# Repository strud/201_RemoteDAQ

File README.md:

# 201_RemoteDAQ
DAQ module with wireless connectivity and local storage

Objectives
1. High resolution low noise analog input capture at rates of at least 5kHz
2. Suitable to take signal inputs of strain gauges/load cells and thermocouples directly without additional pre-amplification
3. At least 4 channels
4. Configuration, live view and download over wireless interface(s)
5. Low channel count (>= 4) of digital outputs, 5A capacity with self protection (ie against short cct)
6. Output channels to have continuity test inputs
7. Internall logging capability at full acquisition rate for at least 30s duration
8. logged file retrieval to be over wireless link &/or to removable SD card

Useful references

https://www.ti.com/product/ADS131M04

https://www.ti.com/lit/ug/sbau332a/sbau332a.pdf

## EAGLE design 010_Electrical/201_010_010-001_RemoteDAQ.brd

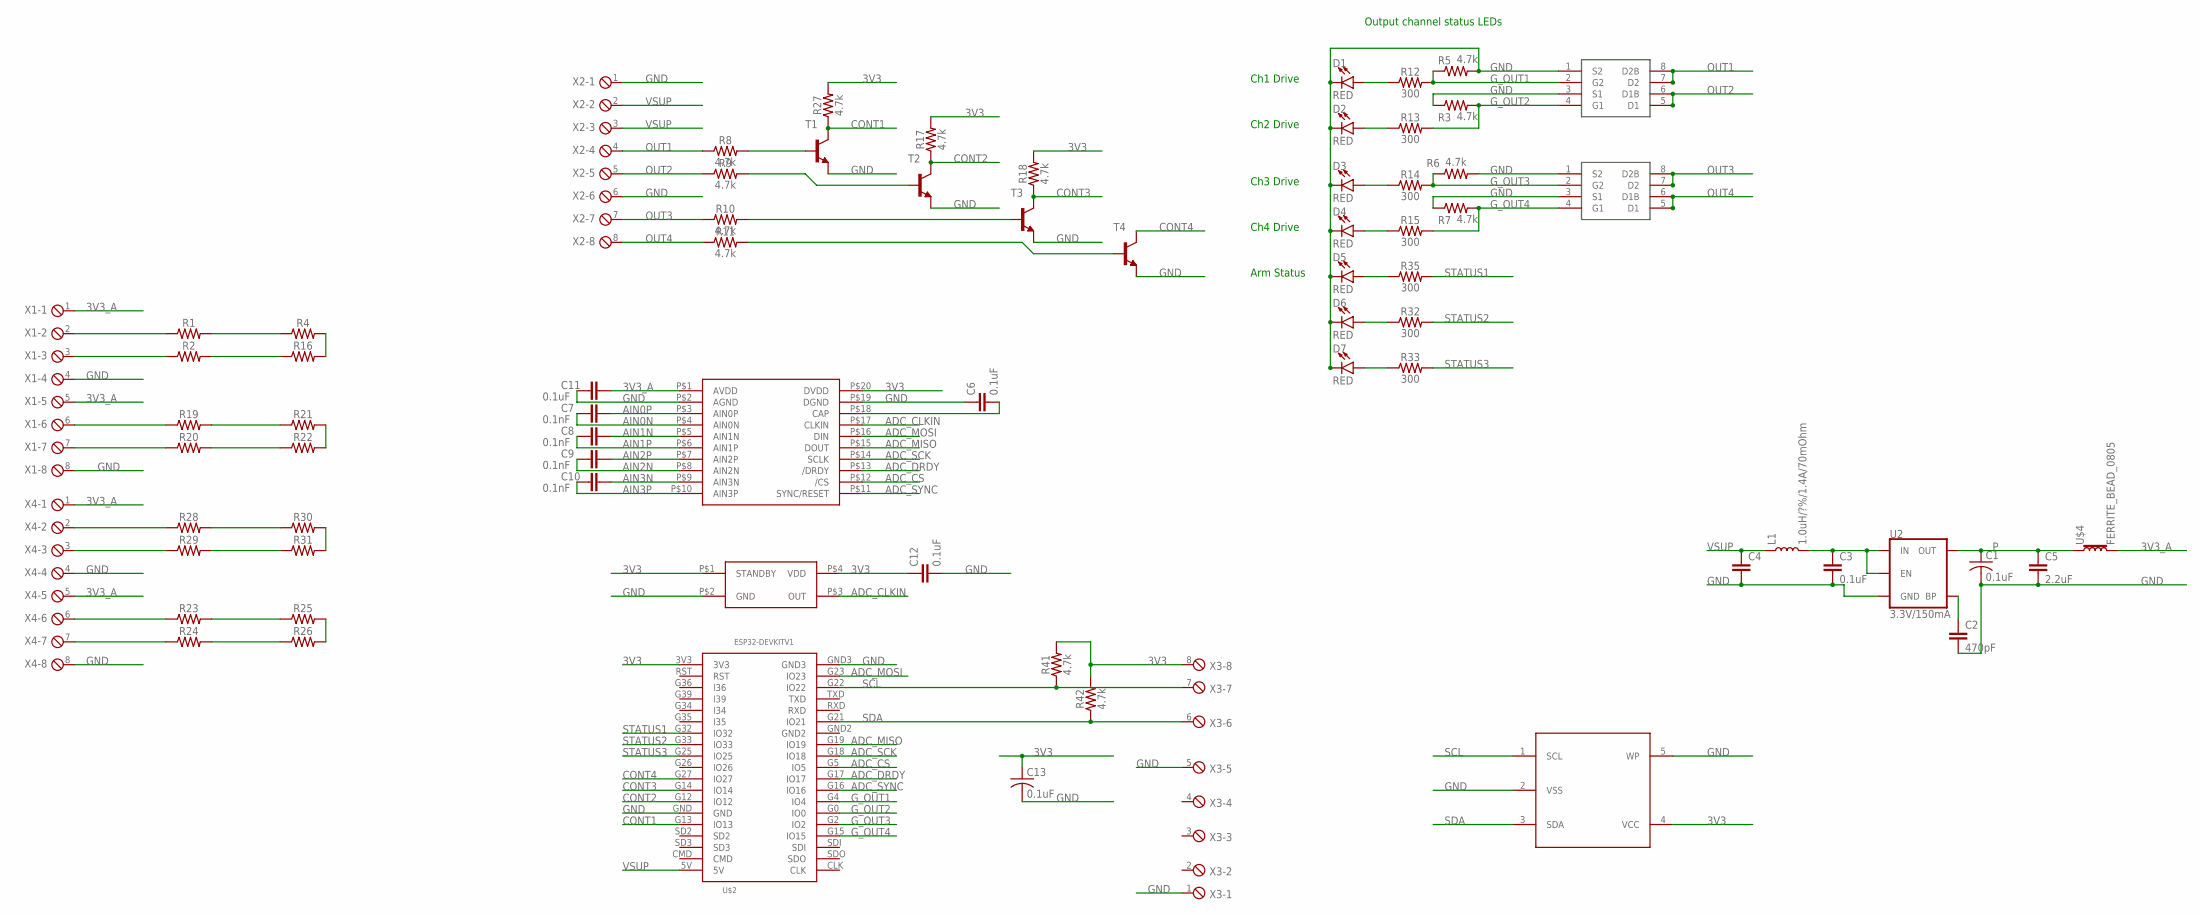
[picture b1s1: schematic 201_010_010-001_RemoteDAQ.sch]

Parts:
C1, C13: 0.1uF; C0603K
C2: 470pF; 0603
C3, C6, C11, C12: 0.1uF; 0603
C4: CAP-0603; 0603
C5: 2.2uF; 0805
C7, C8, C9, C10: 0.1nF; 0603
D1, D2, D3, D4, D5, D6, D7: RED; LED-0603
L1: 1.0uH/?%/1.4A/70mOhm; 0805-WIDE
R1, R2, R4, R16, R19, R20, R21, R22, R23, R24, R25, R26, R28, R29, R30, R31: 0603
R3, R5, R6, R7, R8, R9, R10, R11, R17, R18, R27, R41, R42: 4.7k; 0603
R12, R13, R14, R15, R32, R33, R35: 300; 0603
T1, T2, T3, T4: BC849-NPN-SOT23-BEC; SOT23-BEC
U2: 3.3V/150mA; SOT23-5
U$1: ADS131M04; TSSOP-20
U$2: ESP32DEVKITV1; ESP32-DEVKITV1
U$3, U$5: AO4806; SO08
U$4: FERRITE_BEAD_0805; 0805
U$6: DSC1033; 7X5_PP
U$7: 24AA16T; SOT23-5L
X1, X2, X3, X4: MPT8; 8POL254

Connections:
3V3: C12.1, C13.1, R17.2, R18.2, R27.2, R41.2, R42.2, U$1.P$20 (DVDD), U$2.3V3, U$6.P$1 (STANDBY), U$6.P$4 (VDD), U$7.4 (VCC), X3.8
3V3_A: C11.2, U$1.P$1 (AVDD), U$4.2, X1.1, X1.5, X4.1, X4.5
ADC_CLKIN: U$1.P$17 (CLKIN), U$6.P$3 (OUT)
ADC_CS: U$1.P$12 (/CS), U$2.G5 (IO5)
ADC_DRDY: U$1.P$13 (/DRDY), U$2.G17 (IO17)
ADC_MISO: U$1.P$15 (DOUT), U$2.G19 (IO19)
ADC_MOSI: U$1.P$16 (DIN), U$2.G23 (IO23)
ADC_SCK: U$1.P$14 (SCLK), U$2.G18 (IO18)
ADC_SYNC: U$1.P$11 (SYNC/RESET), U$2.G16 (IO16)
AIN0N: C7.1, R2.2, R16.1, U$1.P$4 (AIN0N)
AIN0P: C7.2, R1.2, R4.1, U$1.P$3 (AIN0P)
AIN1N: C8.2, R20.2, R22.1, U$1.P$5 (AIN1N)
AIN1P: C8.1, R19.2, R21.1, U$1.P$6 (AIN1P)
AIN2N: C9.1, R24.2, R26.1, U$1.P$8 (AIN2N)
AIN2P: C9.2, R23.2, R25.1, U$1.P$7 (AIN2P)
AIN3N: C10.2, R29.2, R31.1, U$1.P$9 (AIN3N)
AIN3P: C10.1, R28.2, R30.1, U$1.P$10 (AIN3P)
CONT1: R27.1, T1.C, U$2.G13 (IO13)
CONT2: R17.1, T2.C, U$2.G12 (IO12)
CONT3: R18.1, T3.C, U$2.G14 (IO14)
CONT4: T4.C, U$2.G27 (IO27)
GND: C1.2, C2.2, C3.2, C4.2, C5.2, C6.1, C11.1, C12.2, C13.2, D1.C, D2.C, D3.C, D4.C, D5.C, D6.C, D7.C, R3.1, R5.2, R6.2, R7.1, T1.E, T2.E, T3.E, T4.E, U2.2 (GND), U$1.P$2 (AGND), U$1.P$19 (DGND), U$2.GND, U$2.GND3, U$3.1 (S2), U$3.3 (S1), U$5.1 (S2), U$5.3 (S1), U$6.P$2 (GND), U$7.2 (VSS), U$7.5 (WP), X1.4, X1.8, X2.1, X2.6, X3.1, X3.5, X4.4, X4.8
G_OUT1: R5.1, R12.2, U$2.G4 (IO4), U$3.2 (G2)
G_OUT2: R3.2, R13.2, U$2.G0 (IO0), U$3.4 (G1)
G_OUT3: R6.1, R14.2, U$2.G2 (IO2), U$5.2 (G2)
G_OUT4: R7.2, R15.2, U$2.G15 (IO15), U$5.4 (G1)
unnamed: C2.1, U2.4 (BP)
unnamed: C3.1, L1.2, U2.1 (IN), U2.3 (EN)
unnamed: R8.2, T1.B
unnamed: R9.2, T2.B
unnamed: R1.1, X1.2
unnamed: R10.2, T3.B
unnamed: R11.2, T4.B
unnamed: D1.A, R12.1
unnamed: D2.A, R13.1
unnamed: R2.1, X1.3
unnamed: R19.1, X1.6
unnamed: D3.A, R14.1
unnamed: D4.A, R15.1
unnamed: C6.2, U$1.P$18 (CAP)
unnamed: R20.1, X1.7
unnamed: R4.2, R16.2
unnamed: R21.2, R22.2
unnamed: R28.1, X4.2
unnamed: R29.1, X4.3
unnamed: R25.2, R26.2
unnamed: R23.1, X4.6
unnamed: D5.A, R35.1
unnamed: R24.1, X4.7
unnamed: R30.2, R31.2
unnamed: D6.A, R32.1
unnamed: D7.A, R33.1
OUT1: R8.1, U$3.7 (D2), U$3.8 (D2B), X2.4
OUT2: R9.1, U$3.5 (D1), U$3.6 (D1B), X2.5
OUT3: R10.1, U$5.7 (D2), U$5.8 (D2B), X2.7
OUT4: R11.1, U$5.5 (D1), U$5.6 (D1B), X2.8
P: C1.1, C5.1, U2.5 (OUT), U$4.1
SCL: R41.1, U$2.G22 (IO22), U$7.1 (SCL), X3.7
SDA: R42.1, U$2.G21 (IO21), U$7.3 (SDA), X3.6
STATUS1: R35.2, U$2.G32 (IO32)
STATUS2: R32.2, U$2.G33 (IO33)
STATUS3: R33.2, U$2.G25 (IO25)
VSUP: C4.1, L1.1, U$2.5V, X2.2, X2.3

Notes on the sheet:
Output channel status LEDs
Ch1 Drive
Ch2 Drive
Ch3 Drive
Ch4 Drive
Arm Status

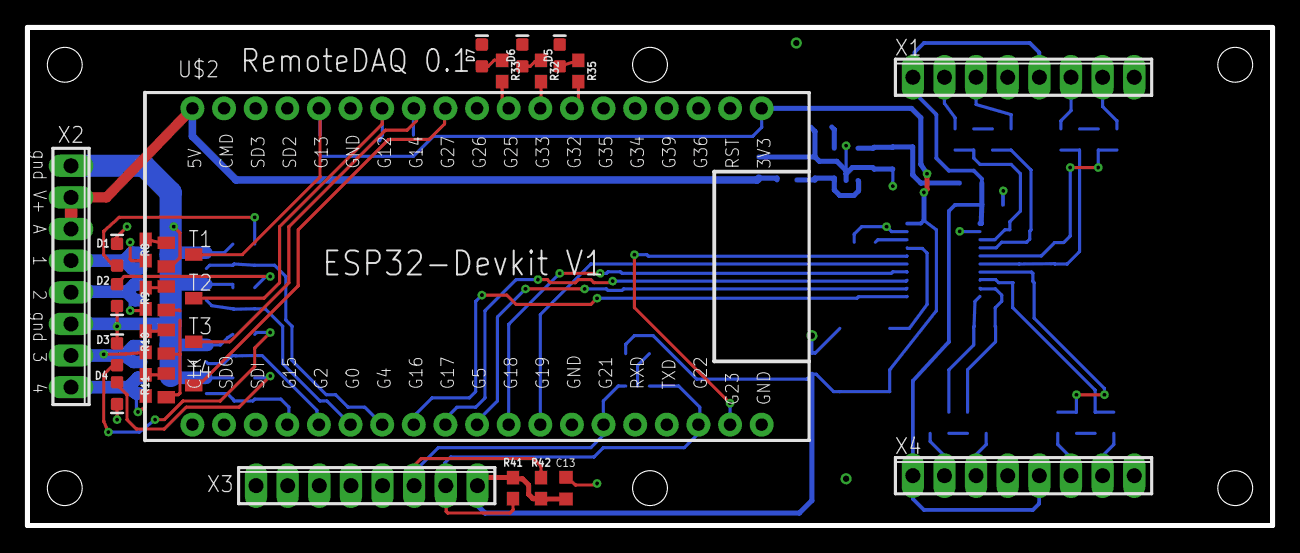
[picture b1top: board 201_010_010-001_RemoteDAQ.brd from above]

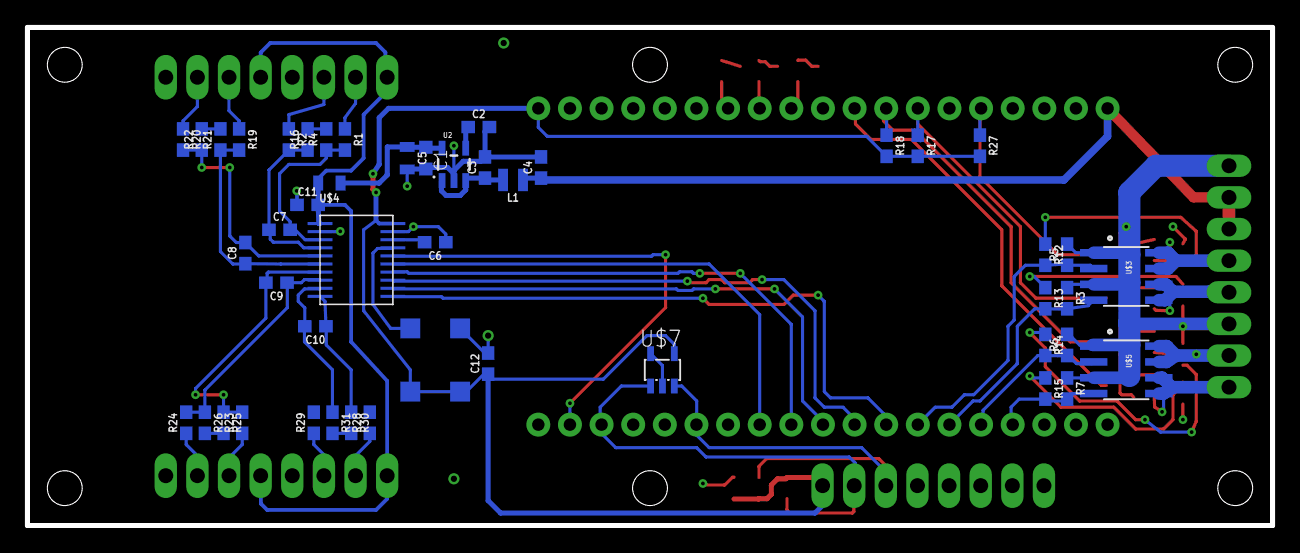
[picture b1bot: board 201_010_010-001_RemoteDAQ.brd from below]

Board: 2 copper layers, 100.0 x 40.0 mm, 73 parts (47 on the bottom side), 63 nets.

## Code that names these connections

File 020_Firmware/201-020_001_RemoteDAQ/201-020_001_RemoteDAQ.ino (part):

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    //#define SPARE   39
    //#define SPARE   34
    //#define SPARE_  35
    #define STATUS1   32
    #define STATUS2   33
    #define STATUS3   25   
    //#define SPARE    26
    #define Cont4Pin    27   // output ch4 continuity measurement
    #define Cont3Pin    14   // output ch3 continuity measurement
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    #define GOut3Pin    2  // output ch3 FET gate drive
    #define GOut2Pin    0  // output ch2 FET gate drive
    #define GOut1Pin    4   // output ch1 FET gate drive
    #define ADC_SYNC    16 // 
    #define ADC_DRDY    17 // 
    #define ADC_CS      5 // 
    #define ADC_SCK     18   // 
    #define ADC_MISO    19    //
    #define SDAPin      21
    #define SCLPin      22
    #define ADC_MOSI    23 // 

// forward declarations

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void updateContinuity(void){
if (digitalRead(Cont1Pin)==LOW) {
    sCont1 = "CC";
    Cont1 = 1;
  }
  else {
    sCont1 = "OC";
    Cont1=0;
  }
  if (digitalRead(Cont2Pin)==LOW) {
    sCont2 = "CC";
    Cont2 = 1;
  }
  else {
    sCont2 = "OC";
    Cont2=0;
  }if (digitalRead(Cont3Pin)==LOW) {
    sCont3 = "CC";
    Cont3 = 1;
  }
  else {
    sCont3 = "OC";
    Cont3=0;
  }
  if (digitalRead(Cont4Pin)==LOW) {
    sCont4 = "CC";
    Cont4 = 1;
  }
  else {
    sCont4 = "OC";
    Cont4=0;
  } 
}
  
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
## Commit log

2020-08-20 Board designs finalised for submission and code port from RocTrak
2020-08-20 Initial code port
    Imported library code from TI
    removed irrelevant code from main file
    added Task for DAQ

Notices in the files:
parts and their libraries:
cs_fets: Licensing: Creative Commons ShareAlike 4.0 International - https://creativecommons.org/licenses/by-sa/4.0
